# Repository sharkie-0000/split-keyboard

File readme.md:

# S Split Keyboard

my 52-key split keyboard design based on two Seeed Studio XIAO RP2040 boards, Cherry MX style mechanical switches and my custom KiCad PCB layout 
each half of keyboard contains 26 keys and its own USB connection, with an additional USB hub to be added in the future

the current repository contains the layout of the PCB, a model of the case, files for production of the board and a demo Arduino firmware
this is just a work-in-progress design and demo, no physical realization or testing has been done yet

[Development journal — 45 estimated hours](JOURNAL.md) · [Parts list](bom.csv)

## how it works

Each controller scans a 5 rows by 6 columns matrix with 26 key points being used and one diode per key
The sample program lowers each row one by one and after detecting stable change sends corresponding character through USB port

```text
26 keys + diodes --> XIAO RP2040 U1 --> USB --> Computer
26 keys + diodes --> XIAO RP2040 U2 --> USB --> Computer
```

Both parts communicate by themselves, there is no connection cable between the controllers that transfers information
Later I plan to use a USB hub to connect both USB cables to my laptop, I have neither designed nor manufactured such hub myself
PCB previews contain a certain amount of board material connecting both key parts, and I still need to resolve this issue in order to allow separate movement of both parts

## main features

- 52 keys with 26 keys on each side and 3 thumb keys in each layout
- 2 XIAO RP2040 microcontrollers with USB separately
- One diode for each switch with Cherry MX 1u PCB mounts
- Wiring on two layers of copper and ground zones
- Four 3.2 mm holes for M3 screws
- Case model in STEP format and STL printing export
- Arduino matrix example with pinout for each controller

## images

these are screenshots of the design and CAD model, i have not built the keyboard yet

## how i plan to build it

this is my strategy for the creation of the circuit; this is only hypothetical since I haven't tested it on the physical board yet

1. sort the diode packaging and the edges of the board, which joins the two halves together and perform schematic and PCB rule checks then export the board files
2. preview the board at the PCB site including the drill holes and the edges of the board before placing your order
3. preview the case and make sure it matches up with the final PCB design and include screw locations, diode locations, and room for USB ports and then perform a test print
4. place the corresponding through-hole diodes in the correct orientation according to the schematic and PCB designs
5. inspect the footprints and clearance around the controllers and switches before placement and ensure there is no unintentional solder connection between pads
6. test each controller and matrix via USB port before assembling the board and installing the keycaps

## firmware demo

open [firmware/firmware.ino](firmware/firmware.ino) in Arduino IDE with a board package that supports XIAO RP2040 and USB Keyboard
set `KEYBOARD_HALF` to `1` if you are working on U1 or `2` if on U2, choose the appropriate board and port, and upload the firmware to each keyboard individually

each half will type the letters `a-z` in the order of the matrix with 10 ms debounce delay
in the demo it will send one character for each press; it doesn't have a typical typing keyboard layout or the ability to hold keys and modifiers yet
the pin configurations in the code have RP2040 GPIO numbers that are not the same as the D pins written on the board

both pin setups passed the C++ syntax validation on the PC using stubbed board libraries, now I need to compile and test them on the actual board

## what is in the repo

```text
.
├── 3d/              Case STEP model and STL export
├── firmware/        Basic Arduino matrix demo
├── gerber/          PCB fabrication exports
├── gerber.zip       Fabrication archive
├── image/           Existing project screenshots
├── journal/         Individual entries and original screenshots
├── journal image/   Copies used by the combined journal
├── kicad/           KiCad design and PCB STEP export
├── bom.csv          Parts, USD prices and purchase links
├── JOURNAL.md       Combined development journal
└── readme.md        Project overview
```

## parts and BOM

i used the parts and USD prices from [bom.csv](bom.csv) for this table
the switches are listed as one pack of 150, the keyboard only needs 52 of them

| Qty | Component | Unit price (USD) | Total (USD) | Link |
|---:|---|---:|---:|---|
| 2 | Seeed Studio XIAO RP2040 v1.0 | $5.64 | $11.28 | [Buy](https://robu.in/product/seeed-studio-xiao-rp2040-v1-0/) |
| 1 | Blank Pudding Keycap Set | $15.99 | $15.99 | [Buy](https://meckeys.com/shop/accessories/keyboard-accessories/keycaps/blank-pudding-keycap-set/) |
| 52 | DIODE-1N4148-SOD-80 (SKU 1415737) | $0.0109 | $0.57 | [Buy](https://robu.in/product/diode-1n4148/) |
| 1 | PCB fabrication (JLCPCB order) | $23.00 | $23.00 | [Buy](https://jlcpcb.com/) |
| 1 | LHGJFKO 3-pin mechanical keyboard switches (150-piece pack) | $18.11 | $18.11 | [Buy](https://www.amazon.in/dp/B0GFDG9GB7) |
| | **Total** | | **$68.95** | |

## PCB and case files

the [Gerber archive](gerber.zip) and [Gerber directory](gerber/) contain the board files i have exported
the picture of the rout indicates no unrouted traces, but i do not have the result which proves that the design rule check is done
check the borders of the final board and export the files once again after making any changes to the design, before sending it for production

the case files are [STEP](3d/s-split-keyboard.step) and [STL](3d/printable-s-split-keyboard.stl)
the [PCB STEP file export](kicad/s-split-keyboard.step) is also provided for comparison of the board and the case
now i have to check how it fits and mount and if there is enough space for cables

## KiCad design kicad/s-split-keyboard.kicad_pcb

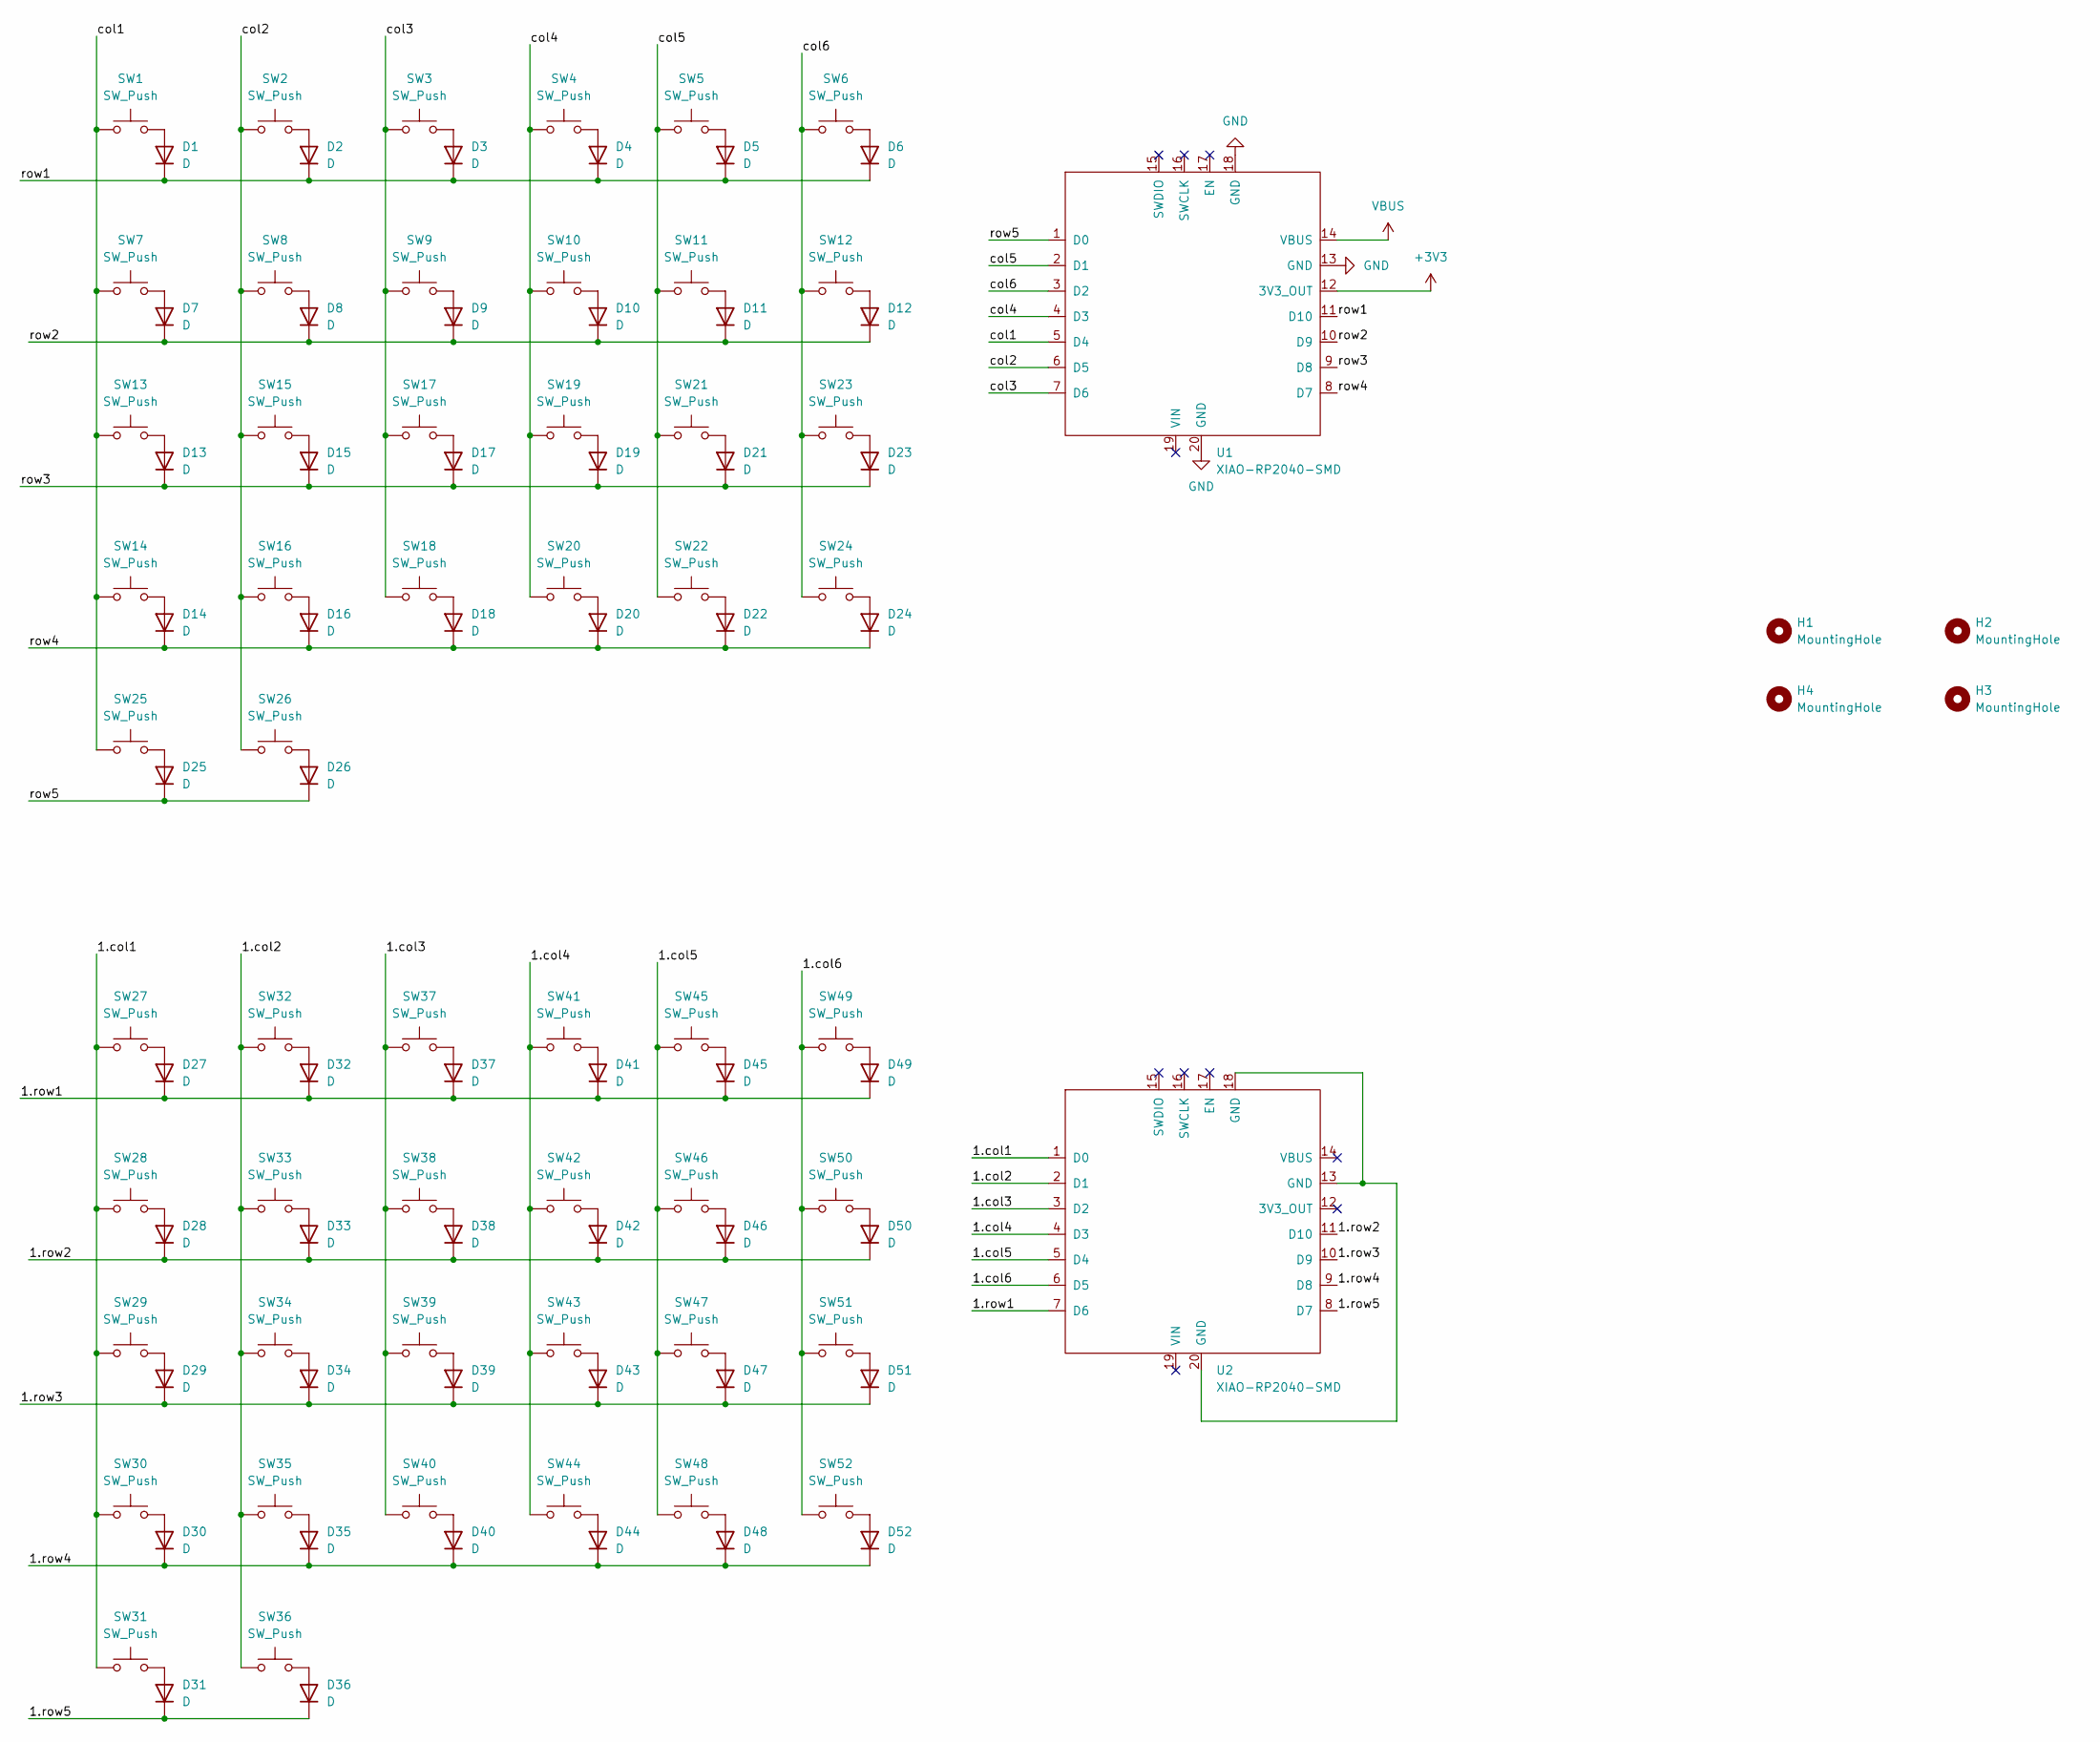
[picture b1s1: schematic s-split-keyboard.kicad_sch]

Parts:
D1, D2, D3, D4, D5, D6, D7, D8, D9, D10, D11, D12, D13, D14, D15, D16, D17, D18, D19, D20, D21, D22, D23, D24, D25, D26, D27, D28, D29, D30, D31, D32, D33, D34, D35, D36, D37, D38, D39, D40, D41, D42, D43, D44, D45, D46, D47, D48, D49, D50, D51, D52: D; D_DO-35_SOD27_P7.62mm_Horizontal
H1, H2, H3, H4: MountingHole; MountingHole_3.2mm_M3
SW1, SW2, SW3, SW4, SW5, SW6, SW7, SW8, SW9, SW10, SW11, SW12, SW13, SW14, SW15, SW16, SW17, SW18, SW19, SW20, SW21, SW22, SW23, SW24, SW25, SW26, SW27, SW28, SW29, SW30, SW31, SW32, SW33, SW34, SW35, SW36, SW37, SW38, SW39, SW40, SW41, SW42, SW43, SW44, SW45, SW46, SW47, SW48, SW49, SW50, SW51, SW52: SW_Push; SW_Cherry_MX_1.00u_PCB
U1, U2: XIAO-RP2040-SMD

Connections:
+3V3: U1.12 (3V3_OUT)
/1.col1: SW27.1, SW28.1, SW29.1, SW30.1, SW31.1, U2.1 (D0)
/1.col2: SW32.1, SW33.1, SW34.1, SW35.1, SW36.1, U2.2 (D1)
/1.col3: SW37.1, SW38.1, SW39.1, SW40.1, U2.3 (D2)
/1.col4: SW41.1, SW42.1, SW43.1, SW44.1, U2.4 (D3)
/1.col5: SW45.1, SW46.1, SW47.1, SW48.1, U2.5 (D4)
/1.col6: SW49.1, SW50.1, SW51.1, SW52.1, U2.6 (D5)
/1.row1: D27.1 (K), D32.1 (K), D37.1 (K), D41.1 (K), D45.1 (K), D49.1 (K), U2.7 (D6)
/1.row2: D28.1 (K), D33.1 (K), D38.1 (K), D42.1 (K), D46.1 (K), D50.1 (K), U2.11 (D10)
/1.row3: D29.1 (K), D34.1 (K), D39.1 (K), D43.1 (K), D47.1 (K), D51.1 (K), U2.10 (D9)
/1.row4: D30.1 (K), D35.1 (K), D40.1 (K), D44.1 (K), D48.1 (K), D52.1 (K), U2.9 (D8)
/1.row5: D31.1 (K), D36.1 (K), U2.8 (D7)
/col1: SW1.1, SW7.1, SW13.1, SW14.1, SW25.1, U1.5 (D4)
/col2: SW2.1, SW8.1, SW15.1, SW16.1, SW26.1, U1.6 (D5)
/col3: SW3.1, SW9.1, SW17.1, SW18.1, U1.7 (D6)
/col4: SW4.1, SW10.1, SW19.1, SW20.1, U1.4 (D3)
/col5: SW5.1, SW11.1, SW21.1, SW22.1, U1.2 (D1)
/col6: SW6.1, SW12.1, SW23.1, SW24.1, U1.3 (D2)
/row1: D1.1 (K), D2.1 (K), D3.1 (K), D4.1 (K), D5.1 (K), D6.1 (K), U1.11 (D10)
/row2: D7.1 (K), D8.1 (K), D9.1 (K), D10.1 (K), D11.1 (K), D12.1 (K), U1.10 (D9)
/row3: D13.1 (K), D15.1 (K), D17.1 (K), D19.1 (K), D21.1 (K), D23.1 (K), U1.9 (D8)
/row4: D14.1 (K), D16.1 (K), D18.1 (K), D20.1 (K), D22.1 (K), D24.1 (K), U1.8 (D7)
/row5: D25.1 (K), D26.1 (K), U1.1 (D0)
GND: U1.13 (GND), U1.18 (GND), U1.20 (GND)
unnamed: D1.2 (A), SW1.2
unnamed: D2.2 (A), SW2.2
unnamed: D3.2 (A), SW3.2
unnamed: D4.2 (A), SW4.2
unnamed: D5.2 (A), SW5.2
unnamed: D6.2 (A), SW6.2
unnamed: D7.2 (A), SW7.2
unnamed: D8.2 (A), SW8.2
unnamed: D9.2 (A), SW9.2
unnamed: D10.2 (A), SW10.2
unnamed: D11.2 (A), SW11.2
unnamed: D12.2 (A), SW12.2
unnamed: D13.2 (A), SW13.2
unnamed: D14.2 (A), SW14.2
unnamed: D15.2 (A), SW15.2
unnamed: D16.2 (A), SW16.2
unnamed: D17.2 (A), SW17.2
unnamed: D18.2 (A), SW18.2
unnamed: D19.2 (A), SW19.2
unnamed: D20.2 (A), SW20.2
unnamed: D21.2 (A), SW21.2
unnamed: D22.2 (A), SW22.2
unnamed: D23.2 (A), SW23.2
unnamed: D24.2 (A), SW24.2
unnamed: D25.2 (A), SW25.2
unnamed: D26.2 (A), SW26.2
unnamed: D27.2 (A), SW27.2
unnamed: D28.2 (A), SW28.2
unnamed: D29.2 (A), SW29.2
unnamed: D30.2 (A), SW30.2
unnamed: D31.2 (A), SW31.2
unnamed: D32.2 (A), SW32.2
unnamed: D33.2 (A), SW33.2
unnamed: D34.2 (A), SW34.2
unnamed: D35.2 (A), SW35.2
unnamed: D36.2 (A), SW36.2
unnamed: D37.2 (A), SW37.2
unnamed: D38.2 (A), SW38.2
unnamed: D39.2 (A), SW39.2
unnamed: D40.2 (A), SW40.2
unnamed: D41.2 (A), SW41.2
unnamed: D42.2 (A), SW42.2
unnamed: D43.2 (A), SW43.2
unnamed: D44.2 (A), SW44.2
unnamed: D45.2 (A), SW45.2
unnamed: D46.2 (A), SW46.2
unnamed: D47.2 (A), SW47.2
unnamed: D48.2 (A), SW48.2
unnamed: D49.2 (A), SW49.2
unnamed: D50.2 (A), SW50.2
unnamed: D51.2 (A), SW51.2
unnamed: D52.2 (A), SW52.2
unnamed: U2.13 (GND), U2.18 (GND), U2.20 (GND)
VBUS: U1.14 (VBUS)

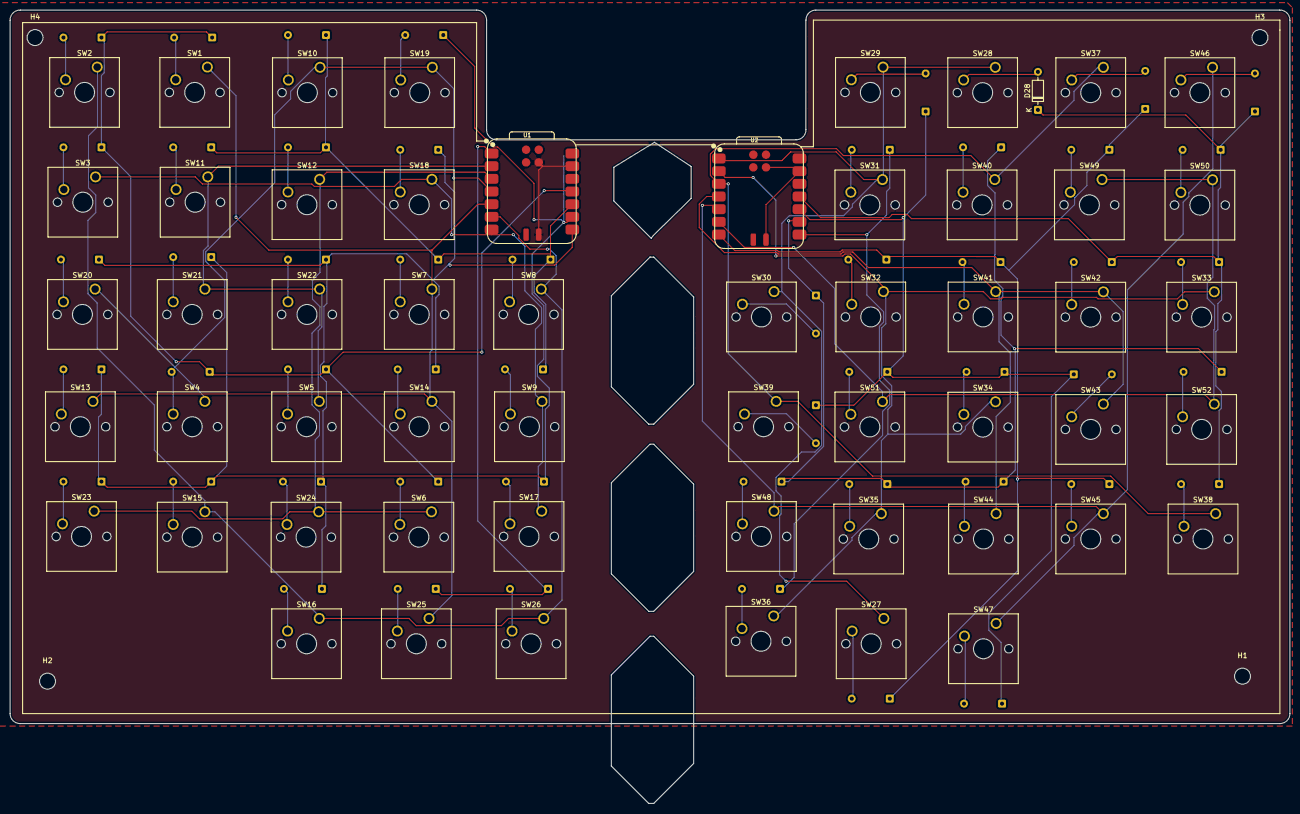
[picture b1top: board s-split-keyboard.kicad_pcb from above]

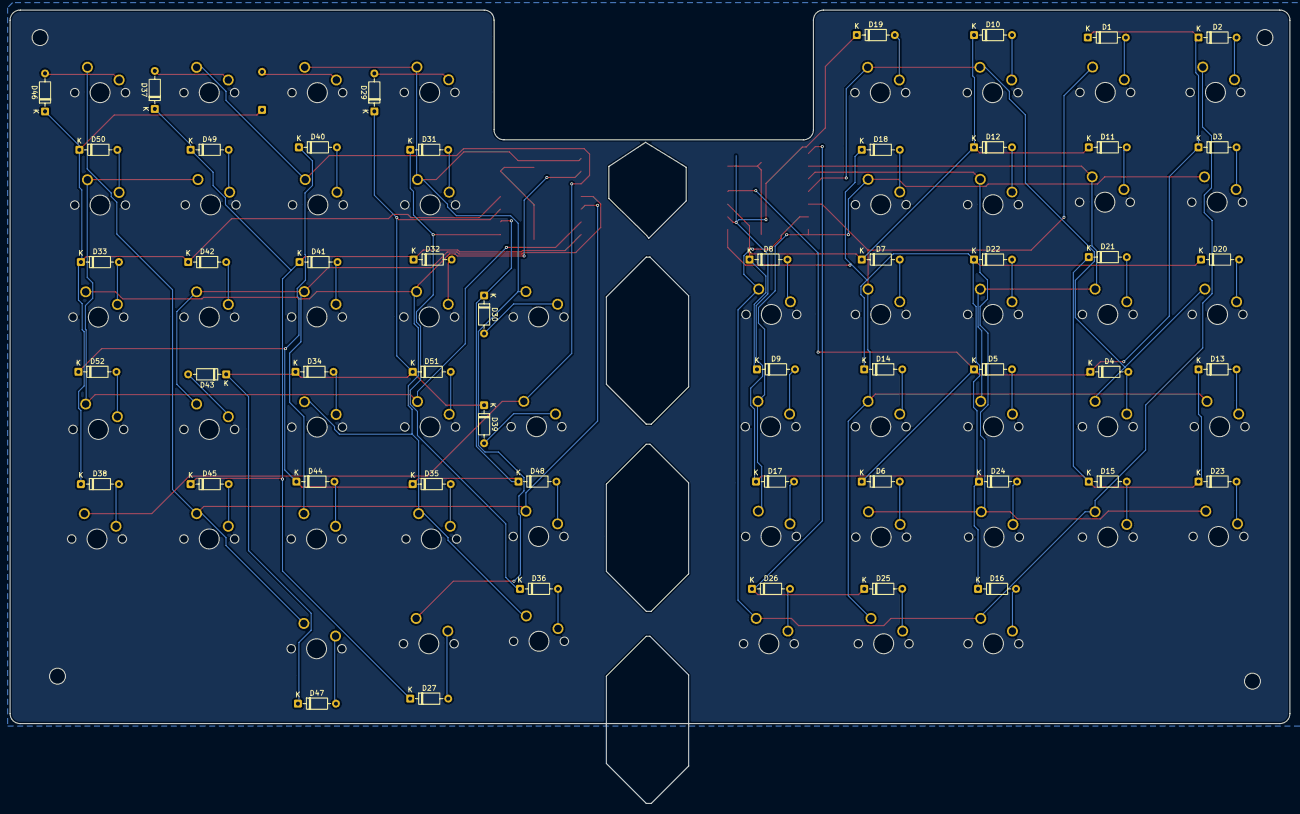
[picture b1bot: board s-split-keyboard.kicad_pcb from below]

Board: 2 copper layers, 256.5 x 143.0 mm, 110 parts (51 on the bottom side), 76 nets.
